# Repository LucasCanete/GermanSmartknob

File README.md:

# German Smartknob
An ESP32-S3 based knob to control smart devices at home. Based on Scott Bez's Smartknob: https://github.com/scottbez1/smartknob?tab=readme-ov-file. Adapted for the standard german wall socket.

## Table of Contents
1. [About the Project](#about-the-project)
2. [Features](#features)
3. [Components](#components)
4. [Getting Started](#getting-started)
5. [Project Status](#project-status)

## About the project
This project mechatronic project has three main parts. The first part consisted of the development of a PCB that could fit in the standard german wall socket and would control sensors, touch display and a BLDC Motor. The second part consisted on 3d printed pieces to sustain the PCB on its place, allow BLDC rotation while keeping the touch display on its place. Finally the third part was the software, which tested that all sensors and actuators worked accordingly. The final product can be seen below. 
<p align="center">
   <br>
   <em>German Smartknob</em>
</p>

## Features
- ESP32-S3 based PCB
- Input Voltage of up to 24V
- Haptic Feedback with a BLDC-Motor (Coming soon)
- Touch Display
- Brightness and Temperature Sensor
- Audio speaker connectors

## Components
A summarized description of this products three main parts.
### PCB
The PCB was designed to fit into the standard german wall socket. It has two sides. 

On the front side there is a ring of RGB Leds for user feedback and at its center a magnetic encoder. The magnetic encoder is key to detect the rotation's direction of the BLDC Motor, that in this project is used as an input device, similar to a rotary encoder. The reason why a BLDC Motor was chosen and not a regular rotary encoder, is because with the first, through proper driver, it is possible to program the motor's torque and adjust it according to the user's use. Besides of this, at the sides of the Front-PCB there are sensors to detect the temperature, the room's brightness and also output audio via a speaker.

<p align="center">
   <br>
   <em>Figure 1: Front side PCB</em>
</p>

On the back side there are connectors available to supply the PCB with 24V, 3.3v and extra outputs with I2C and CAN lines. The Display connector pads, the ESP32-S3, and the audio and bldc driver are also found on the back side of the PCB.

<p align="center">
   <br>
   <em>Figure 2: Backside PCB</em>
</p>

### 3D printed Parts
Using the OnShape CAD tool several 3D pieces were designed, that later were 3d printed. The pieces include a holder for the BLDC Motor to keep it in the middle; a holder for the display, a knob and a case to hide the electronic. Below is an exploded view of the internal pieces of the smartknob.

<p align="center">
   <br>
   <em>Figure 3: Internal Pieces </em>
</p>

### Software
The software was built using the arduino libraries, for simplicities sake. The main goal of the software program was to demonstrate the correct functioning of the main features of the smartknob. Because of this, a small Manu was programmed in which 4 main features can be selected as options. With a tap on the touch display the option can be selected and the functioning of the feature can be demonstrated.

The four menu options and what each of them does is represented with the diagram below:

<p align="center">
   <br>
   <em>Figure 4: Software Diagram </em>
</p>

## Getting Started

### Download this repo
```
git clone https://github.com/LucasCanete/GermanSmartknob.git
```
### Build and upload 

### How To Use

## Project Status
This project is still under development. Eventhough the first version was successful, improvements are still coming to the software side. Some of them are:
- [ ] Full implementation of haptic feedback
- [ ] Connection to smart devices over MQTT, home assistant, etc

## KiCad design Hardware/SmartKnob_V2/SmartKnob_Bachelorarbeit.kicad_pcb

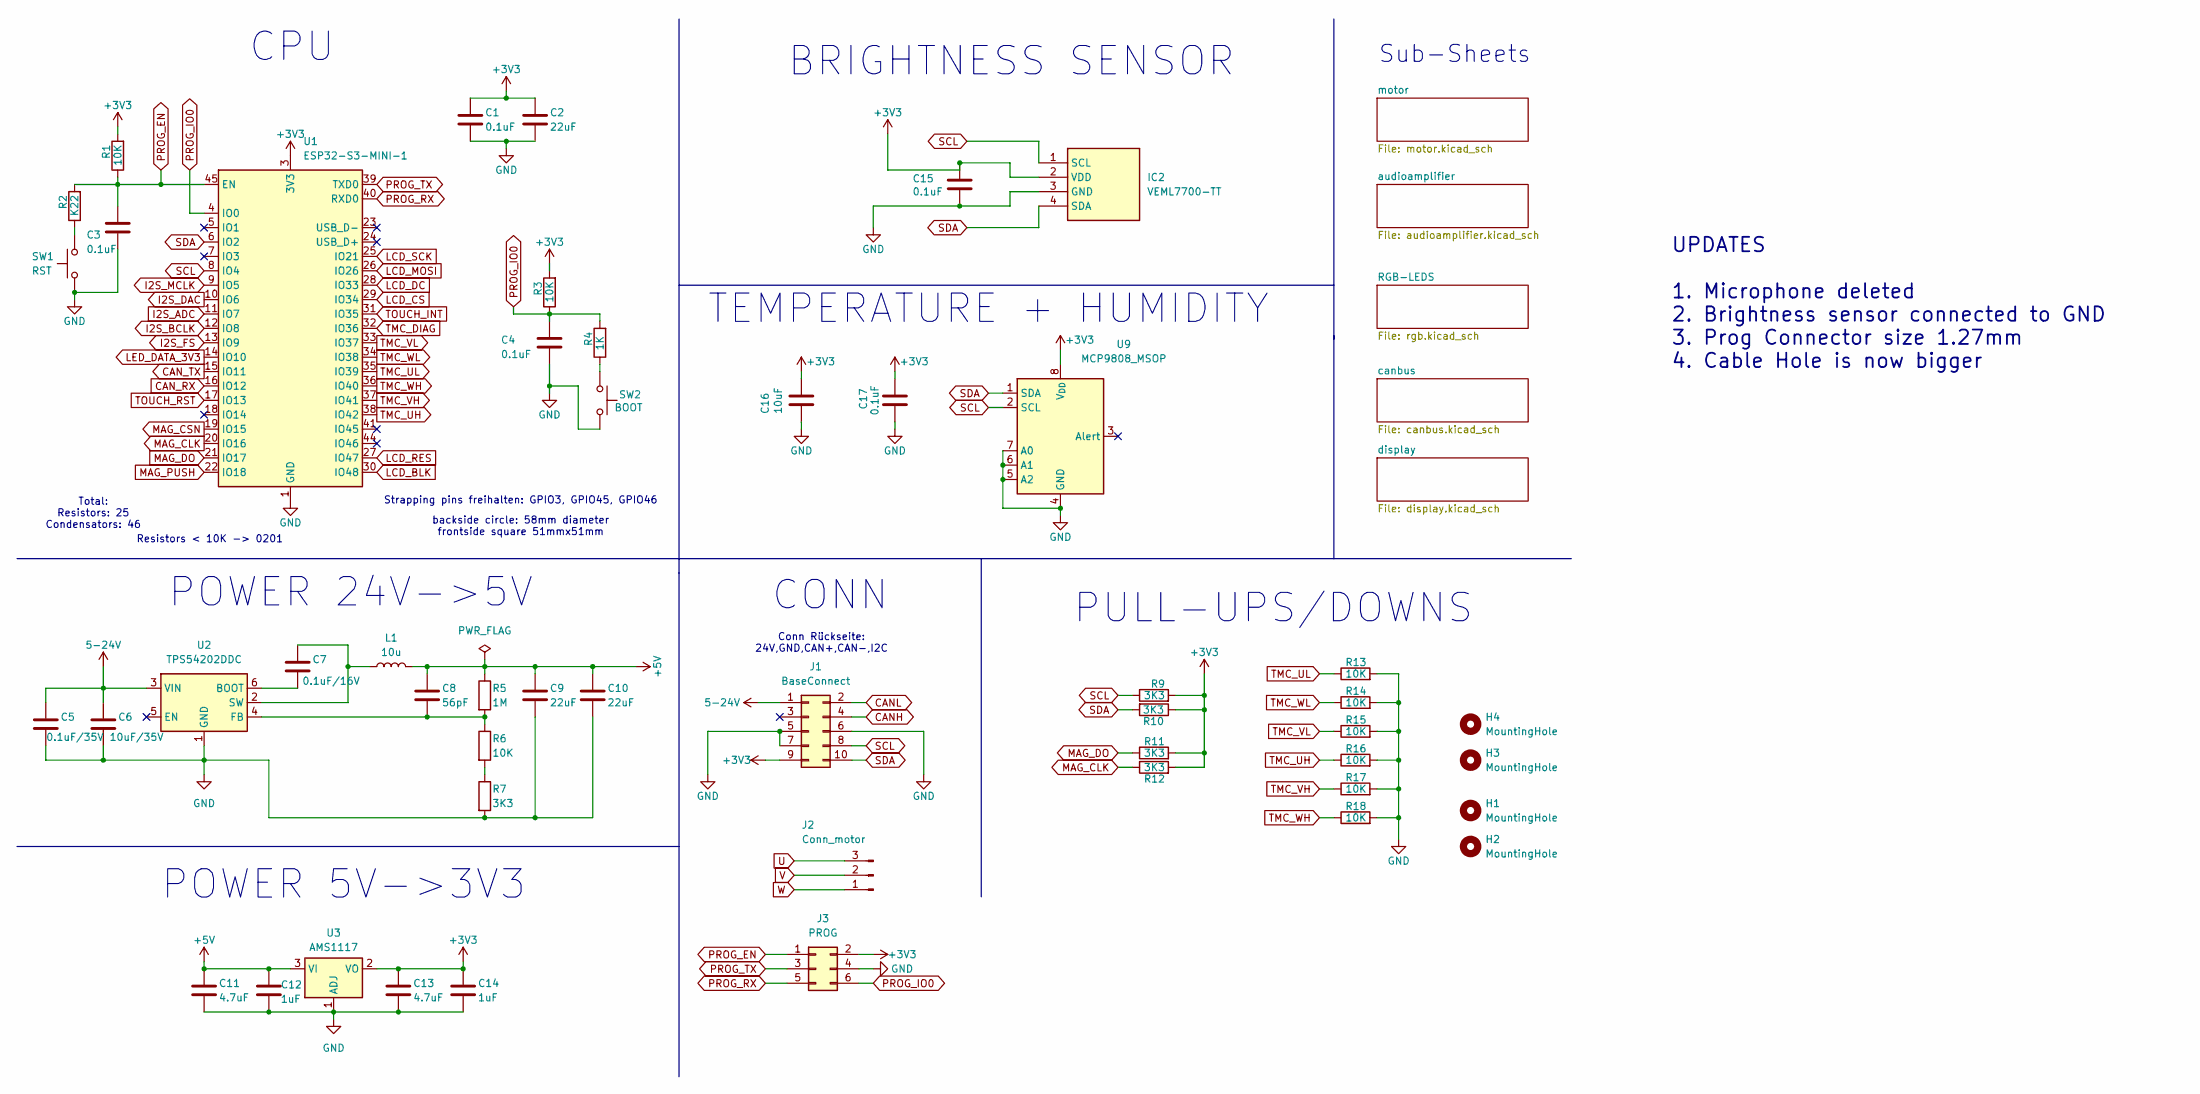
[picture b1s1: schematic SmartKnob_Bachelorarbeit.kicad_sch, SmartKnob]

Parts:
C1: 0.1uF; C_0402_1005Metric
C2: 22uF; C_0402_1005Metric
C3: 0.1uF; C_0402_1005Metric_Pad0.74x0.62mm_HandSolder
C4, C15, C17: 0.1uF; C_0805_2012Metric_Pad1.18x1.45mm_HandSolder
C5: 0.1uF/35V; C_0603_1608Metric
C6: 10uF/35V; C_0805_2012Metric
C7: 0.1uF/16V; C_0603_1608Metric
C8: 56pF; C_0402_1005Metric
C9, C10: 22uF; C_0603_1608Metric
C11, C13: 4.7uF; C_0805_2012Metric_Pad1.18x1.45mm_HandSolder
C12, C14: 1uF; C_0805_2012Metric_Pad1.18x1.45mm_HandSolder
C16: 10uF; C_0805_2012Metric_Pad1.18x1.45mm_HandSolder
H1, H2, H3: MountingHole; MountingHole_2.2mm_M2
H4: MountingHole; MountingHole_2.1mm
IC2: VEML7700-TT; VEML7700; Mouser Part Number 78-VEML7700-TT
J1: BaseConnect; IDC-Header_2x05_P2.54mm_Vertical_SMD
J2: Conn_motor; Molex_PicoBlade_53261-0371_1x03-1MP_P1.25mm_Horizontal
J3: PROG; PinHeader_2x03_P1.27mm_Vertical_SMD
L1: 10u; L_APV_APH0630
R1, R6, R13, R14, R15, R16, R17, R18: 10K; R_0201_0603Metric
R2: K22; R_0805_2012Metric_Pad1.20x1.40mm_HandSolder
R3: 10K; R_0805_2012Metric_Pad1.20x1.40mm_HandSolder
R4: 1K; R_0805_2012Metric_Pad1.20x1.40mm_HandSolder
R5: 1M; R_0402_1005Metric
R7, R9, R10, R11, R12: 3K3; R_0201_0603Metric
SW1: RST; SW_SPST_B3U-1000P
SW2: BOOT; SW_SPST_B3U-1000P
U1: ESP32-S3-MINI-1; ESP32-S2-MINI-1
U2: TPS54202DDC; SOT-23-6
U3: AMS1117; SOT-223-3_TabPin2_HANDSOLDER
U9: MCP9808_MSOP; MSOP-8_3x3mm_P0.65mm

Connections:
5-24V: C5.1, C6.1, J1.1, U2.3 (VIN)
+3V3: C1.1, C2.1, C13.1, C14.1, C15.2, C16.2, C17.2, IC2.2 (VDD), J1.9, J3.2, R1.2, R3.2, R9.2, R10.1, R11.2, R12.2, U1.3 (3V3), U3.2 (VO), U9.8 (V_{DD}); also elsewhere on the board
+5V: C8.1, C9.1, C10.1, C11.1, C12.1, L1.2, R5.1, U3.3 (VI); also elsewhere on the board
CANH: J1.4; also elsewhere on the board
CANL: J1.2; also elsewhere on the board
CAN_RX: U1.16 (IO12); also elsewhere on the board
CAN_TX: U1.15 (IO11); also elsewhere on the board
GND: C1.2, C2.2, C3.2, C4.2, C5.2, C6.2, C9.2, C10.2, C11.2, C12.2, C13.2, C14.2, C15.1, C16.1, C17.1, IC2.3 (GND), J1.5, J1.6, J1.7, J3.4, R7.2, R13.2, R14.2, R15.2, R16.2, R17.2, R18.2, SW1.1, SW2.2, U1.1 (GND), U1.2 (GND), U1.42 (GND), U1.43 (GND), U1.46 (GND), U1.47 (GND), U1.48 (GND), U1.49 (GND), U1.50 (GND), U1.51 (GND), U1.52 (GND), U1.53 (GND), U1.54 (GND), U1.55 (GND), U1.56 (GND), U1.57 (GND), U1.58 (GND), U1.59 (GND), U1.60 (GND), U1.61 (GND), U1.62 (GND), U1.63 (GND), U1.64 (GND), U1.65 (GND), U2.1 (GND), U3.1 (ADJ), U9.4 (GND), U9.5 (A2), U9.6 (A1), U9.7 (A0); also elsewhere on the board
I2S_ADC: U1.11 (IO7); also elsewhere on the board
I2S_BCLK: U1.12 (IO8); also elsewhere on the board
I2S_DAC: U1.10 (IO6); also elsewhere on the board
I2S_FS: U1.13 (IO9); also elsewhere on the board
I2S_MCLK: U1.9 (IO5); also elsewhere on the board
LCD_BLK: U1.30 (IO48); also elsewhere on the board
LCD_CS: U1.29 (IO34); also elsewhere on the board
LCD_DC: U1.28 (IO33); also elsewhere on the board
LCD_MOSI: U1.26 (IO26); also elsewhere on the board
LCD_RES: U1.27 (IO47); also elsewhere on the board
LCD_SCK: U1.25 (IO21); also elsewhere on the board
LED_DATA_3V3: U1.14 (IO10); also elsewhere on the board
MAG_CLK: R12.1, U1.20 (IO16); also elsewhere on the board
MAG_CSN: U1.19 (IO15); also elsewhere on the board
MAG_DO: R11.1, U1.21 (IO17); also elsewhere on the board
MAG_PUSH: U1.22 (IO18); also elsewhere on the board
unnamed: R2.1, SW1.2
unnamed: R4.1, SW2.1
unnamed: R6.2, R7.1
unnamed: C7.2, U2.6 (BOOT)
unnamed: C8.2, R5.2, R6.1, U2.4 (FB)
unnamed: C7.1, L1.1, U2.2 (SW)
PROG_EN: C3.1, J3.1, R1.1, R2.2, U1.45 (EN)
PROG_IO0: C4.1, J3.6, R3.1, R4.2, U1.4 (IO0)
PROG_RX: J3.5, U1.40 (RXD0)
PROG_TX: J3.3, U1.39 (TXD0)
SCL: IC2.1 (SCL), J1.8, R9.1, U1.8 (IO4), U9.2 (SCL); also elsewhere on the board
SDA: IC2.4 (SDA), J1.10, R10.2, U1.6 (IO2), U9.1 (SDA); also elsewhere on the board
TMC_DIAG: U1.32 (IO36); also elsewhere on the board
TMC_UH: R16.1, U1.38 (IO42); also elsewhere on the board
TMC_UL: R13.1, U1.35 (IO39); also elsewhere on the board
TMC_VH: R17.1, U1.37 (IO41); also elsewhere on the board
TMC_VL: R15.1, U1.33 (IO37); also elsewhere on the board
TMC_WH: R18.1, U1.36 (IO40); also elsewhere on the board
TMC_WL: R14.1, U1.34 (IO38); also elsewhere on the board
TOUCH_INT: U1.31 (IO35); also elsewhere on the board
TOUCH_RST: U1.17 (IO13); also elsewhere on the board
U: J2.3; also elsewhere on the board
V: J2.2; also elsewhere on the board
W: J2.1; also elsewhere on the board

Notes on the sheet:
Sub-Sheets
TEMPERATURE + HUMIDITY
Total: Resistors: 25 Condensators: 46
POWER 5V->3V3
CONN
CPU
Conn Rückseite: 24V,GND,CAN+,CAN-,I2C
BRIGHTNESS SENSOR
Resistors < 10K -> 0201
Strapping pins freihalten: GPIO3, GPIO45, GPIO46
backside circle: 58mm diameter frontside square 51mmx51mm
UPDATES 1. Microphone deleted 2. Brightness sensor connected to GND 3. Prog Connector size 1.27mm 4. Cable Hole is now bigger
POWER 24V->5V
PULL-UPS/DOWNS

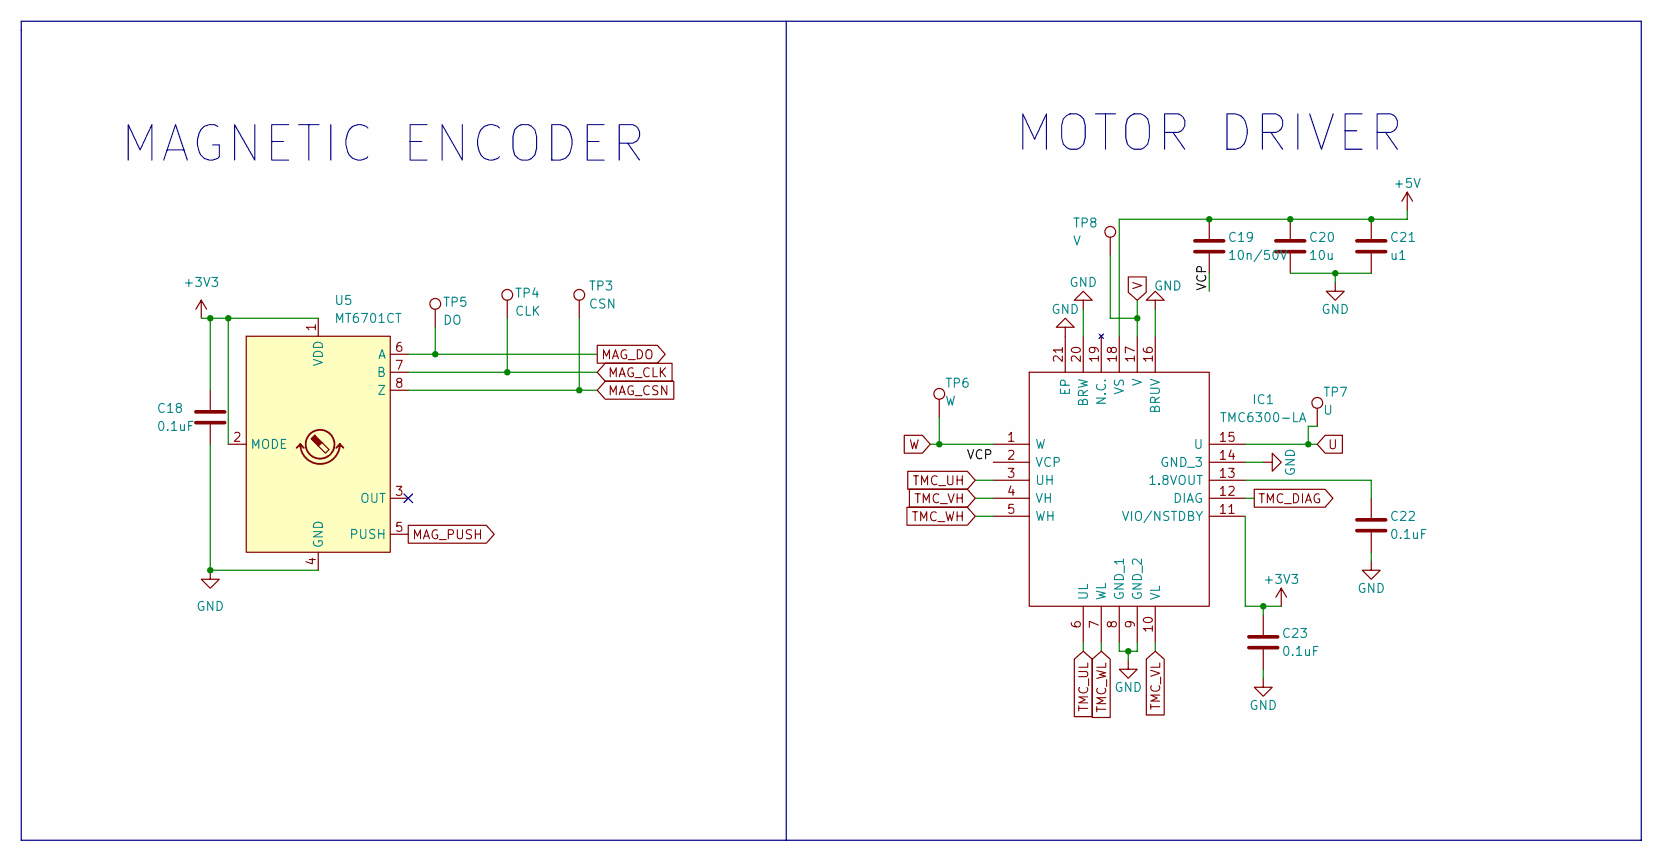
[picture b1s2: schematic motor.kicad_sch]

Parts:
C18: 0.1uF; C_0805_2012Metric_Pad1.18x1.45mm_HandSolder
C19: 10n/50V; C_0402_1005Metric
C20: 10u; C_0402_1005Metric
C21: u1; C_0402_1005Metric
C22, C23: 0.1uF; C_0402_1005Metric
IC1: TMC6300-LA; QFN40P300X300X90-21N; Mouser Part Number 700-TMC6300-LA
TP3: CSN; TestPoint_Pad_D2.0mm
TP4: CLK; TestPoint_Pad_D2.0mm
TP5: DO; TestPoint_Pad_D2.0mm
TP6: W; TestPoint_Pad_D2.0mm
TP7: U; TestPoint_Pad_D2.0mm
TP8: V; TestPoint_Pad_D2.0mm
U5: MT6701CT; SO-8_3.9x4.9mm_P1.27mm

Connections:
+3V3: C18.1, C23.1, IC1.11 (VIO/NSTDBY), U5.1 (VDD), U5.2 (MODE); also elsewhere on the board
+5V: C19.1, C20.1, C21.1, IC1.18 (VS); also elsewhere on the board
/motor/VCP: C19.2, IC1.2 (VCP)
GND: C18.2, C20.2, C21.2, C22.2, C23.2, IC1.8 (GND_1), IC1.9 (GND_2), IC1.14 (GND_3), IC1.16 (BRUV), IC1.20 (BRW), IC1.21 (EP), U5.4 (GND); also elsewhere on the board
MAG_CLK: TP4.1, U5.7 (B); also elsewhere on the board
MAG_CSN: TP3.1, U5.8 (Z); also elsewhere on the board
MAG_DO: TP5.1, U5.6 (A); also elsewhere on the board
MAG_PUSH: U5.5 (PUSH); also elsewhere on the board
unnamed: C22.1, IC1.13 (1.8VOUT)
TMC_DIAG: IC1.12 (DIAG); also elsewhere on the board
TMC_UH: IC1.3 (UH); also elsewhere on the board
TMC_UL: IC1.6 (UL); also elsewhere on the board
TMC_VH: IC1.4 (VH); also elsewhere on the board
TMC_VL: IC1.10 (VL); also elsewhere on the board
TMC_WH: IC1.5 (WH); also elsewhere on the board
TMC_WL: IC1.7 (WL); also elsewhere on the board
U: IC1.15 (U), TP7.1; also elsewhere on the board
V: IC1.17 (V), TP8.1; also elsewhere on the board
W: IC1.1 (W), TP6.1; also elsewhere on the board

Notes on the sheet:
MOTOR DRIVER
MAGNETIC ENCODER

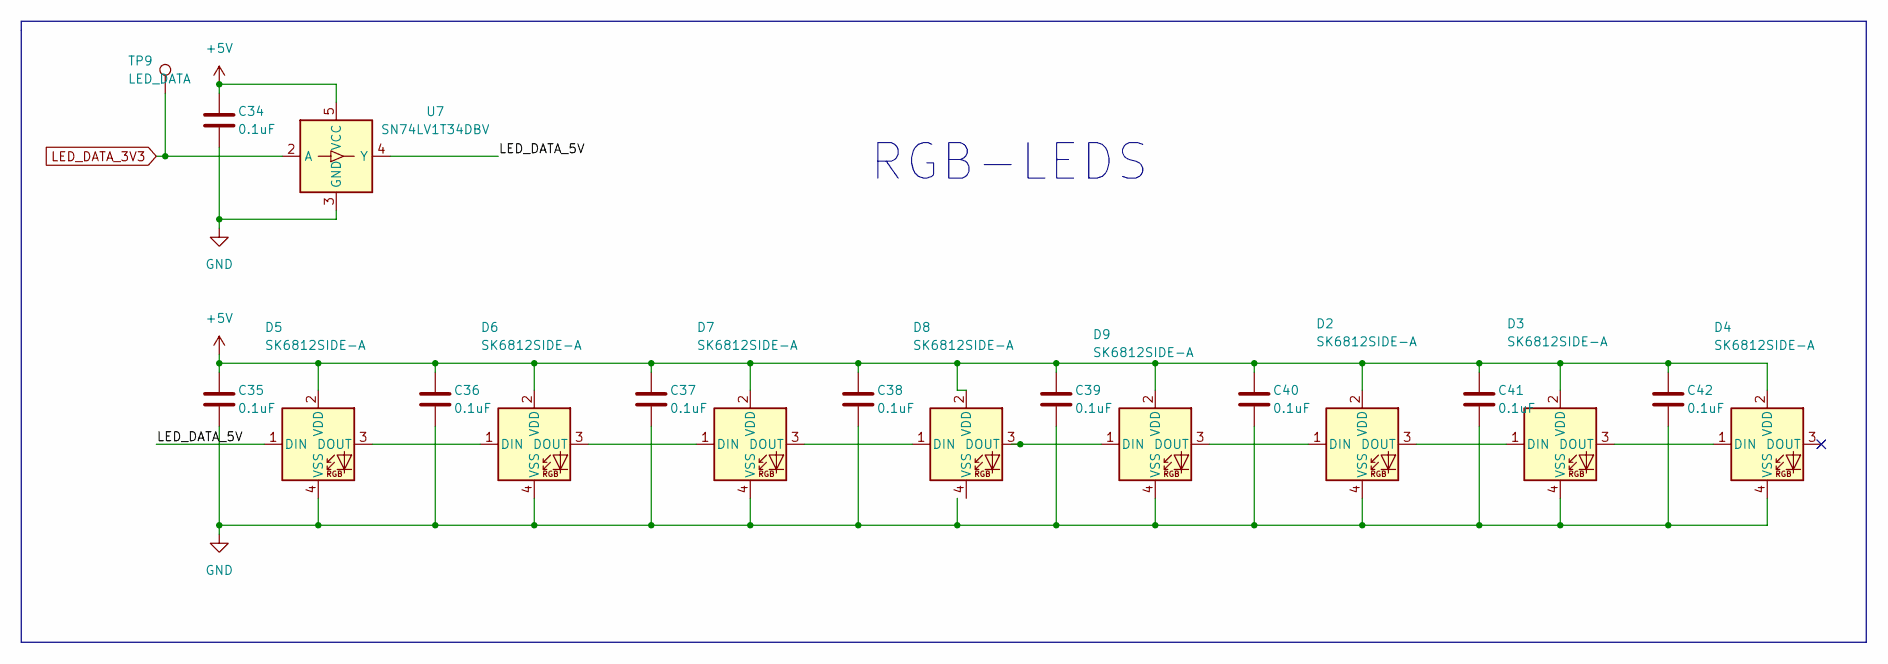
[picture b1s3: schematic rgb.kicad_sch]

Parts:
C34: 0.1uF; C_0402_1005Metric
C35, C36, C37, C38, C39, C40, C41, C42: 0.1uF; C_0805_2012Metric_Pad1.18x1.45mm_HandSolder
D2, D3, D4, D5, D6, D7, D8, D9: SK6812SIDE-A; SK6812_SIDE_A_handsolder; Digikey 1528-4691-ND
TP9: LED_DATA; TestPoint_Pad_D2.0mm
U7: SN74LV1T34DBV; SOT-23-5

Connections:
+5V: C34.1, C35.1, C36.1, C37.1, C38.1, C39.1, C40.1, C41.1, C42.1, D2.2 (VDD), D3.2 (VDD), D4.2 (VDD), D5.2 (VDD), D6.2 (VDD), D7.2 (VDD), D8.2 (VDD), D9.2 (VDD), U7.5 (VCC); also elsewhere on the board
/RGB-LEDS/LED_DATA_5V: D5.1 (DIN), U7.4 (Y)
GND: C34.2, C35.2, C36.2, C37.2, C38.2, C39.2, C40.2, C41.2, C42.2, D2.4 (VSS), D3.4 (VSS), D4.4 (VSS), D5.4 (VSS), D6.4 (VSS), D7.4 (VSS), D9.4 (VSS), U7.3 (GND); also elsewhere on the board
LED_DATA_3V3: TP9.1, U7.2 (A); also elsewhere on the board
unnamed: D2.1 (DIN), D9.3 (DOUT)
unnamed: D2.3 (DOUT), D3.1 (DIN)
unnamed: D3.3 (DOUT), D4.1 (DIN)
unnamed: D5.3 (DOUT), D6.1 (DIN)
unnamed: D6.3 (DOUT), D7.1 (DIN)
unnamed: D7.3 (DOUT), D8.1 (DIN)
unnamed: D8.3 (DOUT), D9.1 (DIN)

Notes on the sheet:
RGB-LEDS

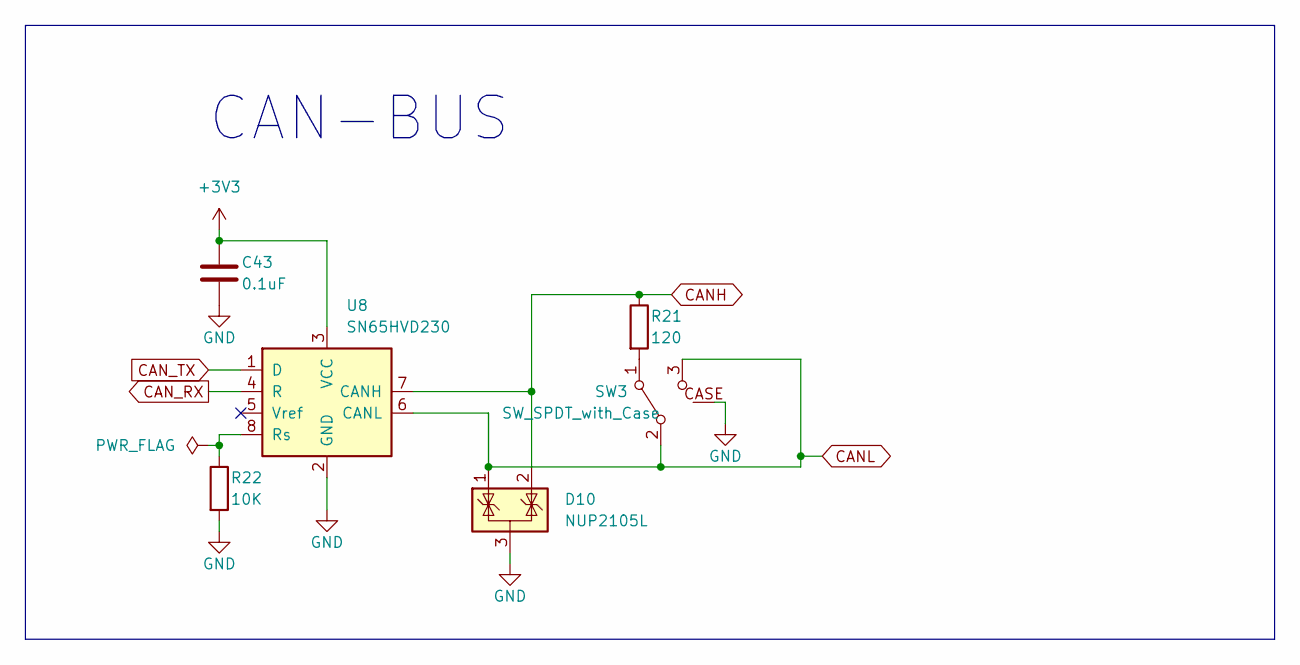
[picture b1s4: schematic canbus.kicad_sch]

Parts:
C43: 0.1uF; C_0402_1005Metric
D10: NUP2105L; SOT-23
R21: 120; R_0201_0603Metric
R22: 10K; R_0201_0603Metric
SW3: SW_SPDT_with_Case; SW_SPDT_PCM12_handsolder
U8: SN65HVD230; SOIC-8_3.9x4.9mm_P1.27mm

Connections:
+3V3: C43.1, U8.3 (VCC); also elsewhere on the board
CANH: D10.2 (K), R21.1, U8.7 (CANH); also elsewhere on the board
CANL: D10.1 (K), SW3.2 (B), SW3.3 (C), U8.6 (CANL); also elsewhere on the board
CAN_RX: U8.4 (R); also elsewhere on the board
CAN_TX: U8.1 (D); also elsewhere on the board
GND: C43.2, D10.3 (A), R22.2, SW3.CASE, U8.2 (GND); also elsewhere on the board
unnamed: R21.2, SW3.1 (A)
unnamed: R22.1, U8.8 (Rs)

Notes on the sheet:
CAN-BUS

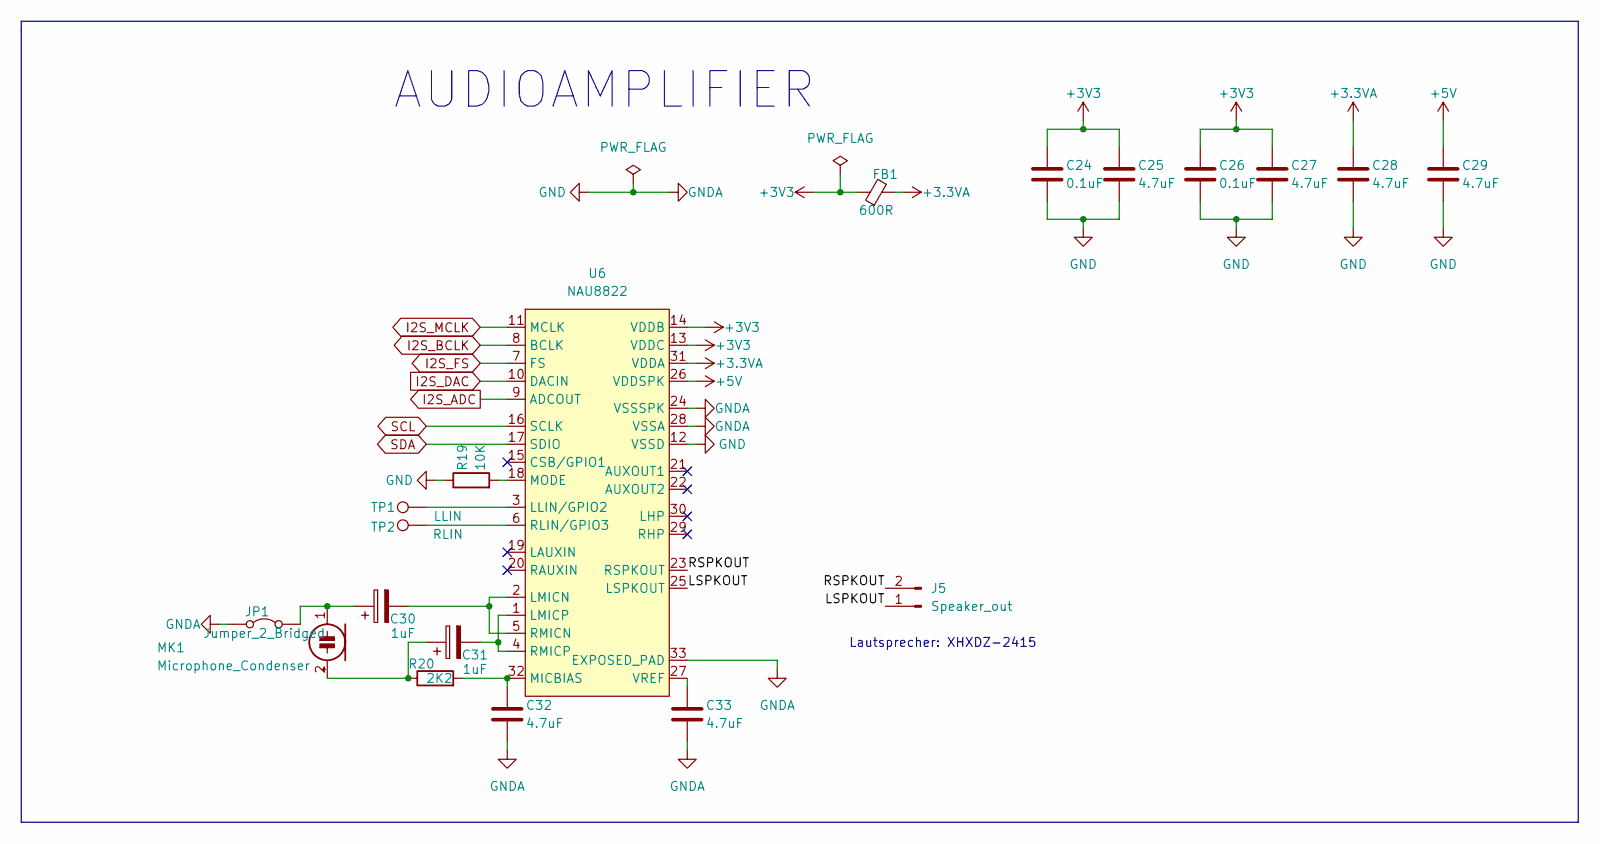
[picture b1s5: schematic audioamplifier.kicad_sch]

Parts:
C24, C26: 0.1uF; C_0402_1005Metric
C25, C27, C28, C29, C32, C33: 4.7uF; C_0402_1005Metric
C30, C31: 1uF; CP_EIA-2012-12_Kemet-R
FB1: 600R; L_0603_1608Metric
J5: Speaker_out; SolderPads_2mm_2
JP1: Jumper_2_Bridged; SolderJumper-2_P1.3mm_Bridged2Bar_RoundedPad1.0x1.5mm
MK1: Microphone_Condenser; POM-2244P-C3310-2-R
R19: 10K; R_0201_0603Metric
R20: 2K2; R_0201_0603Metric
TP1: LLIN; TestPoint_Pad_D2.0mm
TP2: RLIN; TestPoint_Pad_D2.0mm
U6: NAU8822; QFN-32-1EP_5x5mm_P0.5mm_EP3.6x3.6mm_ThermalVias

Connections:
+3.3VA: C28.1, FB1.2, U6.31 (VDDA)
+3V3: C24.1, C25.1, C26.1, C27.1, FB1.1, U6.13 (VDDC), U6.14 (VDDB); also elsewhere on the board
+5V: C29.1, U6.26 (VDDSPK); also elsewhere on the board
/audioamplifier/LSPKOUT: J5.1, U6.25 (LSPKOUT)
/audioamplifier/RSPKOUT: J5.2, U6.23 (RSPKOUT)
GND: C24.2, C25.2, C26.2, C27.2, C28.2, C29.2, C32.2, C33.2, JP1.1 (A), R19.1, U6.12 (VSSD), U6.24 (VSSSPK), U6.28 (VSSA), U6.33 (EXPOSED_PAD); also elsewhere on the board
I2S_ADC: U6.9 (ADCOUT); also elsewhere on the board
I2S_BCLK: U6.8 (BCLK); also elsewhere on the board
I2S_DAC: U6.10 (DACIN); also elsewhere on the board
I2S_FS: U6.7 (FS); also elsewhere on the board
I2S_MCLK: U6.11 (MCLK); also elsewhere on the board
unnamed: C30.1, JP1.2 (B), MK1.1 (-)
unnamed: C31.1, MK1.2 (+), R20.1
unnamed: TP1.1, U6.3 (LLIN/GPIO2)
unnamed: C30.2, U6.2 (LMICN), U6.5 (RMICN)
unnamed: C31.2, U6.1 (LMICP), U6.4 (RMICP)
unnamed: C32.1, R20.2, U6.32 (MICBIAS)
unnamed: R19.2, U6.18 (MODE)
unnamed: TP2.1, U6.6 (RLIN/GPIO3)
unnamed: C33.1, U6.27 (VREF)
SCL: U6.16 (SCLK); also elsewhere on the board
SDA: U6.17 (SDIO); also elsewhere on the board

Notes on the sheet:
Lautsprecher: XHXDZ-2415
AUDIOAMPLIFIER

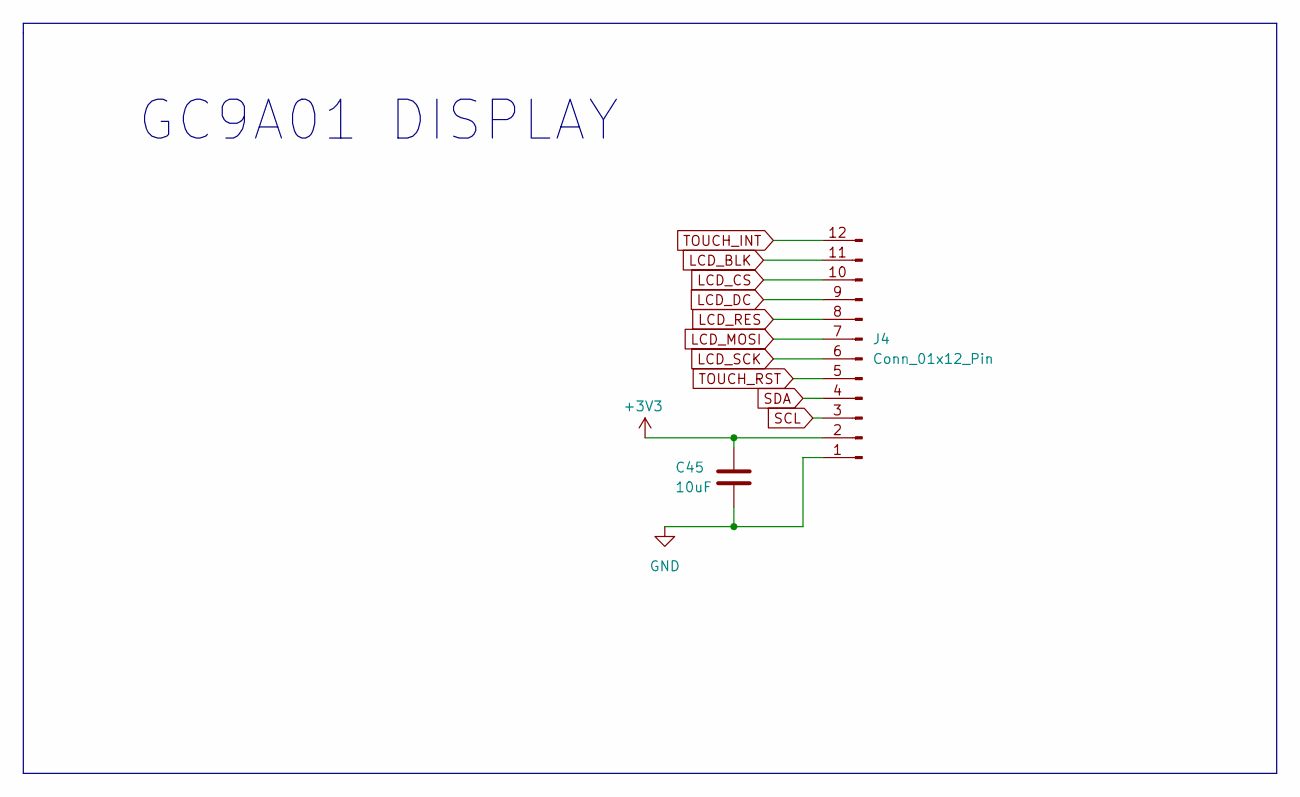
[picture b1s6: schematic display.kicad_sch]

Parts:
C45: 10uF; C_0402_1005Metric
J4: Conn_01x12_Pin; SolderPads_2mm_12

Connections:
+3V3: C45.1, J4.2; also elsewhere on the board
GND: C45.2, J4.1; also elsewhere on the board
LCD_BLK: J4.11; also elsewhere on the board
LCD_CS: J4.10; also elsewhere on the board
LCD_DC: J4.9; also elsewhere on the board
LCD_MOSI: J4.7; also elsewhere on the board
LCD_RES: J4.8; also elsewhere on the board
LCD_SCK: J4.6; also elsewhere on the board
SCL: J4.3; also elsewhere on the board
SDA: J4.4; also elsewhere on the board
TOUCH_INT: J4.12; also elsewhere on the board
TOUCH_RST: J4.5; also elsewhere on the board

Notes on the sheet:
GC9A01 DISPLAY

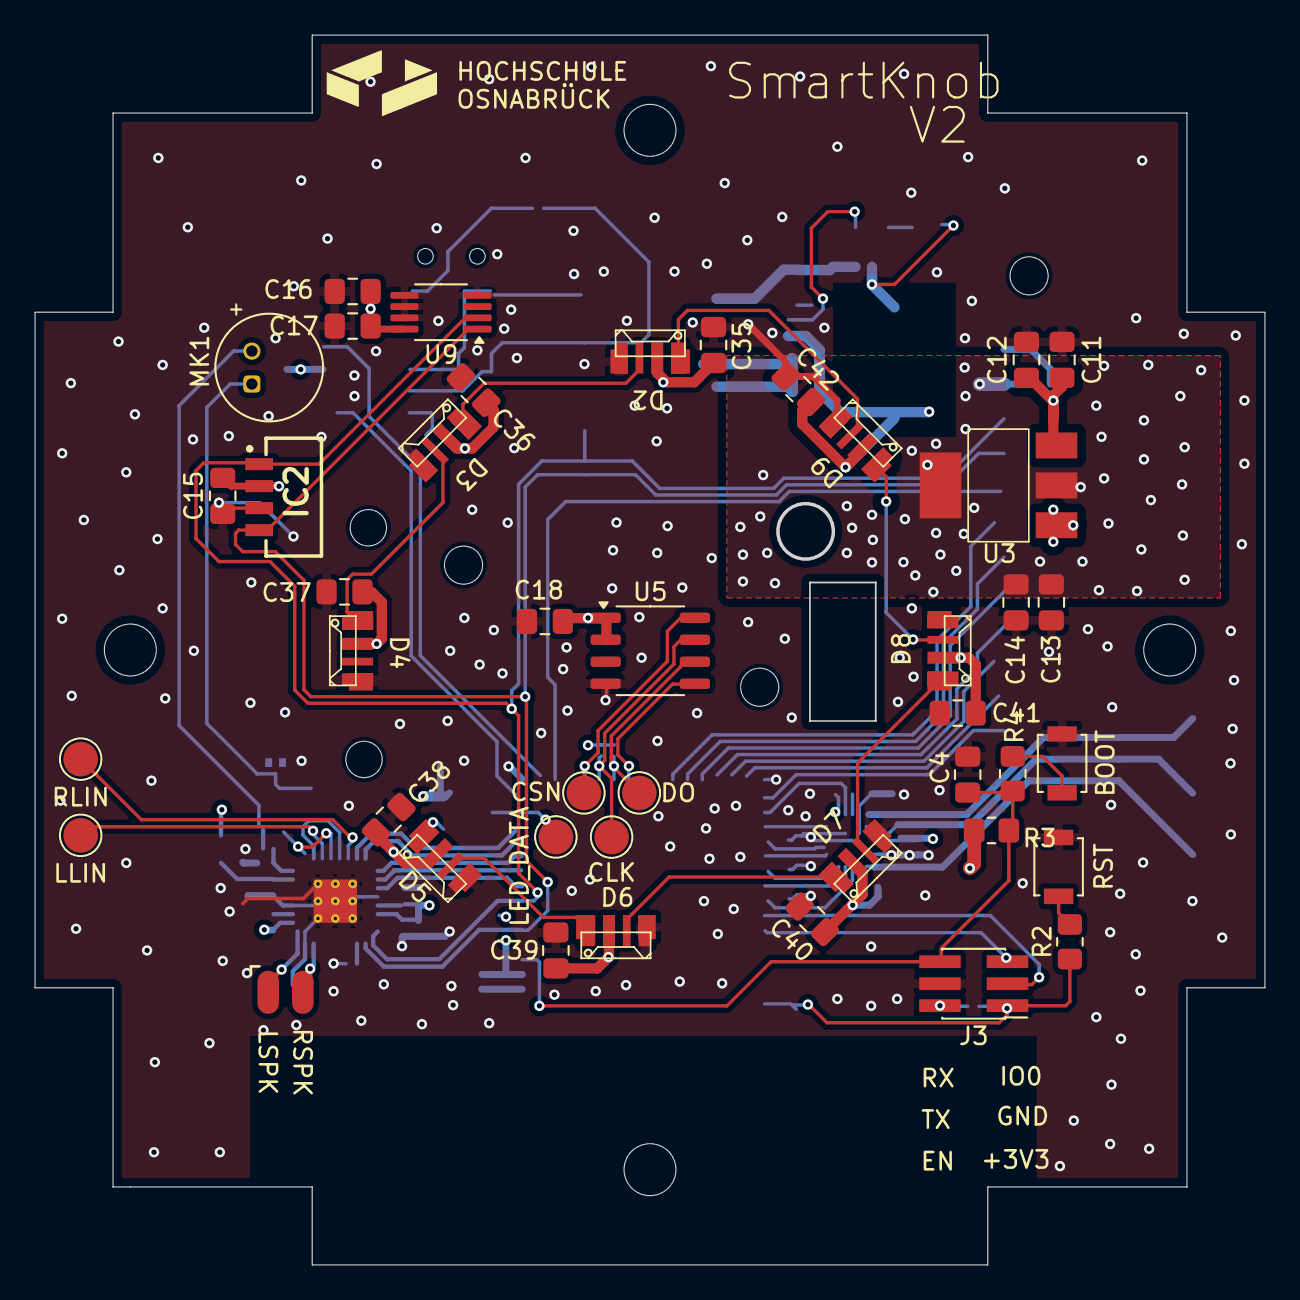
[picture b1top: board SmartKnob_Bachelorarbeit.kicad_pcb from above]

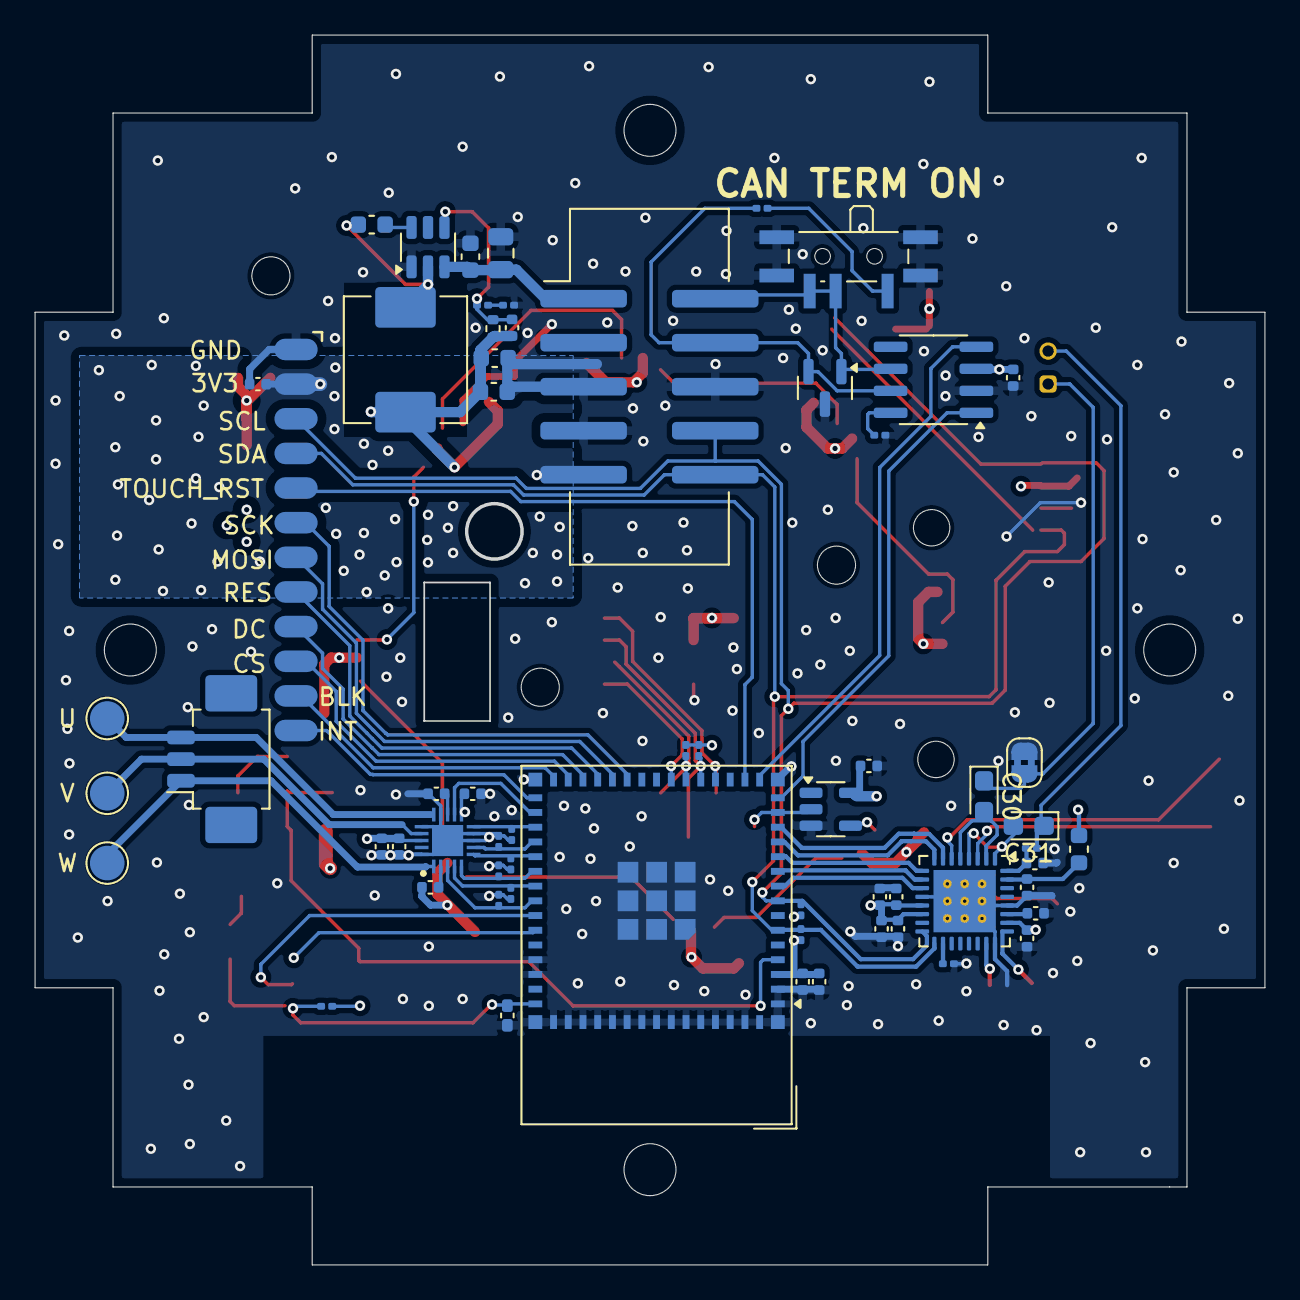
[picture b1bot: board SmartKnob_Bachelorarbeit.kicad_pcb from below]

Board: 4 copper layers, 70.9 x 70.9 mm, 110 parts (62 on the bottom side), 72 nets.

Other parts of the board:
H4#2: MountingHole; MountingHole_2.1mm

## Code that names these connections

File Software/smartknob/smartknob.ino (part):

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#define TFT_RST  47

//MOTOR PINS
#define TMC_UH 42
#define TMC_VH 41
#define TMC_WH 40
#define TMC_UL 39
#define TMC_VL 37
#define TMC_WL 38

// Temperature Sensor, Light Sensor, Touch Controller
#define SDA 2
#define SCL 4

#define TOUCH_RST 13
#define TOUCH_INT 35

//MAGNETIC ENCODER
#define SDA_ME 17
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  pixels.begin();

  //Initialize Touch Controller
  pinMode(TOUCH_RST, OUTPUT);//first reset the controller
  digitalWrite(TOUCH_RST, LOW);
  delay(5);
  digitalWrite(TOUCH_RST, HIGH);  
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
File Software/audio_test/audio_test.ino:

extern "C" {
#include "driver/i2c_master.h"
}

#include "FreeRTOS.h"
#include "task.h"
#include <nau88c22.hh>
#include <AudioPlayer.hh>
#include "fanfare.h"
#include <HardwareSerial.h>
//#include <Wire.h> issues when including Wire.h conflicts with i2c_new_master_bus


#define AUDIO 1


HardwareSerial mySerial(1); 

//PINS
constexpr gpio_num_t PIN_I2C_SDA = (gpio_num_t)2;
constexpr gpio_num_t PIN_I2C_SCL = (gpio_num_t)4;

constexpr gpio_num_t PIN_I2S_MCLK = (gpio_num_t)5;
constexpr gpio_num_t PIN_I2S_FS = (gpio_num_t)9;
constexpr gpio_num_t PIN_I2S_DAC = (gpio_num_t)6;
constexpr gpio_num_t PIN_I2S_ADC = (gpio_num_t)7;
constexpr gpio_num_t PIN_I2S_BCLK = (gpio_num_t)8;


// Global variables
AudioPlayer::Player *mp3player{nullptr};
i2c_master_bus_handle_t i2c_master_handle{nullptr};




void audioTask(void *pvParameters){
  
  while(1){
    mp3player->Loop();
    }

  
 }

    void AudioLoop(void *pvParameters){
        TickType_t lastWakeTime;
        const TickType_t FREQUENCY = pdMS_TO_TICKS(20);
        while(mp3player){
            xTaskDelayUntil( &lastWakeTime, FREQUENCY);
            mp3player->Loop();
        }
    }

void setup() {

mySerial.begin(115200, SERIAL_8N1, 44, 43);


   
    // I2C configuration
    i2c_master_bus_config_t i2c_mst_config = {
        .i2c_port = I2C_NUM_0,
        .sda_io_num = PIN_I2C_SDA,
        .scl_io_num = PIN_I2C_SCL,
        .clk_source = I2C_CLK_SRC_DEFAULT,
        .glitch_ignore_cnt = 7,
        .intr_priority=0,
        .trans_queue_depth=0,
        .flags={
            .enable_internal_pullup=1,
        }
    };

    // Initialize I2C
    esp_err_t err = i2c_new_master_bus(&i2c_mst_config, &i2c_master_handle);
    if (err != ESP_OK) {
        // Handle error
    }

    //Initialize codec and player
    nau88c22::M *codec = new nau88c22::M(i2c_master_handle, PIN_I2S_MCLK, PIN_I2S_BCLK, PIN_I2S_FS, PIN_I2S_DAC);
    mp3player = new AudioPlayer::Player(codec);
    mp3player->Init();

    mp3player->PlayMP3(&fanfare_mp3[0], fanfare_mp3_len, 255, true);

    //Task??
    xTaskCreate(audioTask,"AudioTask",8192*4,NULL,1,NULL);
    
}

void loop() {
  #if 0
  
    if(mp3player){
        mp3player->Loop();
       
      }
   #endif

      
 }

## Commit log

2025-09-21 Added images
2025-09-21 Added new images
2025-09-22 New images
